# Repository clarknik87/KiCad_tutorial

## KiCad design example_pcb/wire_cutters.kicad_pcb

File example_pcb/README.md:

# KiCad_tutorial
Basic PCB Design using KiCad. USU SPAC 2020 worksheet

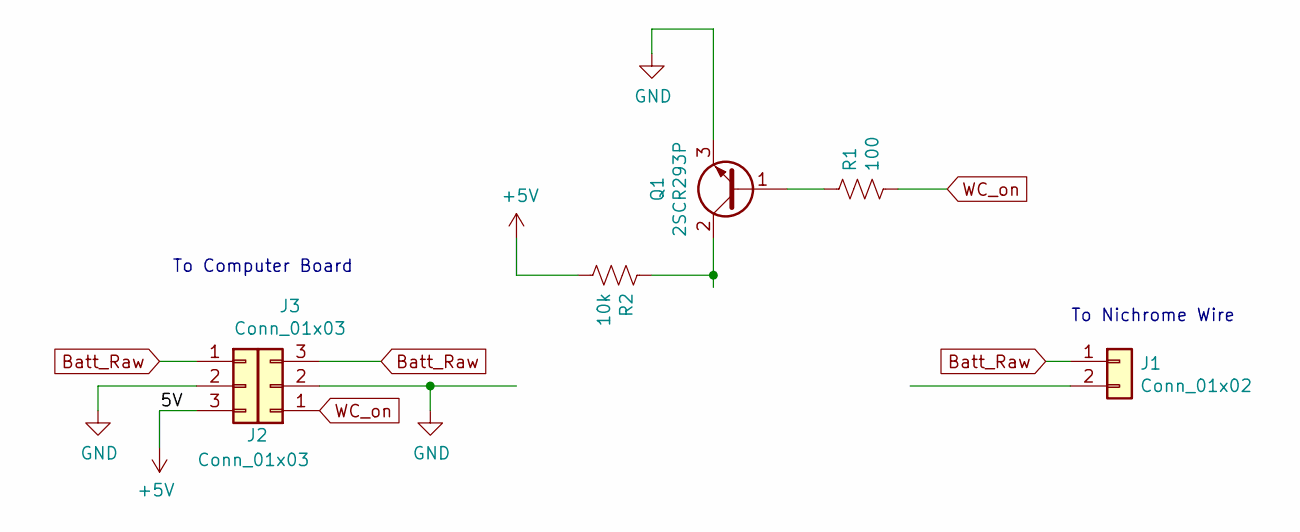
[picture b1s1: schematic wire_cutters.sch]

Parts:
J1: Conn_01x02; SolderWirePad_1x02_P3.81mm_Drill0.8mm
J2, J3: Conn_01x03; SolderWirePad_1x03_P3.175mm_Drill0.8mm
Q1: 2SCR293P; SOT-89
R1: 100; R_1206_3216Metric
R2: 10k; R_1206_3216Metric

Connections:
+5V: J2.3, R2.2
Batt_Raw: J1.1, J2.1, J3.3
GND: J2.2, J3.2, Q1.3 (E)
unnamed: Q1.1 (B), R1.1
unnamed: Q1.2 (C), R2.1
WC_on: J3.1, R1.2

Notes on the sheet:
To Computer Board
To Nichrome Wire

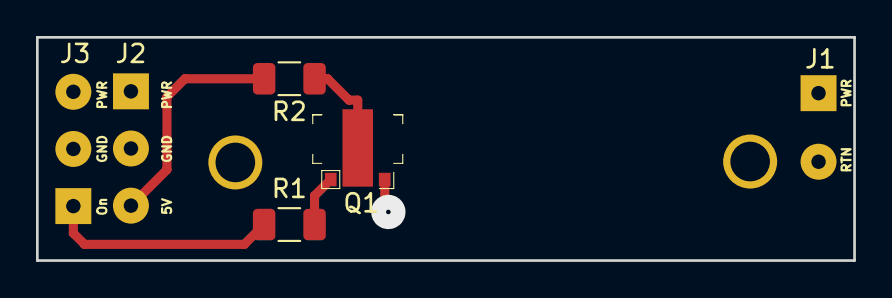
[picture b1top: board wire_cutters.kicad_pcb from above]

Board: 2 copper layers, 45.4 x 12.4 mm, 6 parts (0 on the bottom side), 6 nets.

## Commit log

2019-12-15 Removed extra kicad files and libraries. Added an outline for the tutorial document
2020-03-05 Added a section on traces and vias. Considering whether to end the written portion of the tutorial there
2020-03-06 Final updates to the tutorial and lecture outline documents. Removed odt files and replaced with pdfs
2020-03-09 Removed the N-Channel Resistor from the schematic, netlist, and layout to be added as an example in lecture.
